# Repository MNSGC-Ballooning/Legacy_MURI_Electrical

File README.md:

# LEGACY_MURI_Electrical
Legacy repository containing EAGLE schematics and PCB files for MURI related payloads. For the newest designs, see MURI_Electric.

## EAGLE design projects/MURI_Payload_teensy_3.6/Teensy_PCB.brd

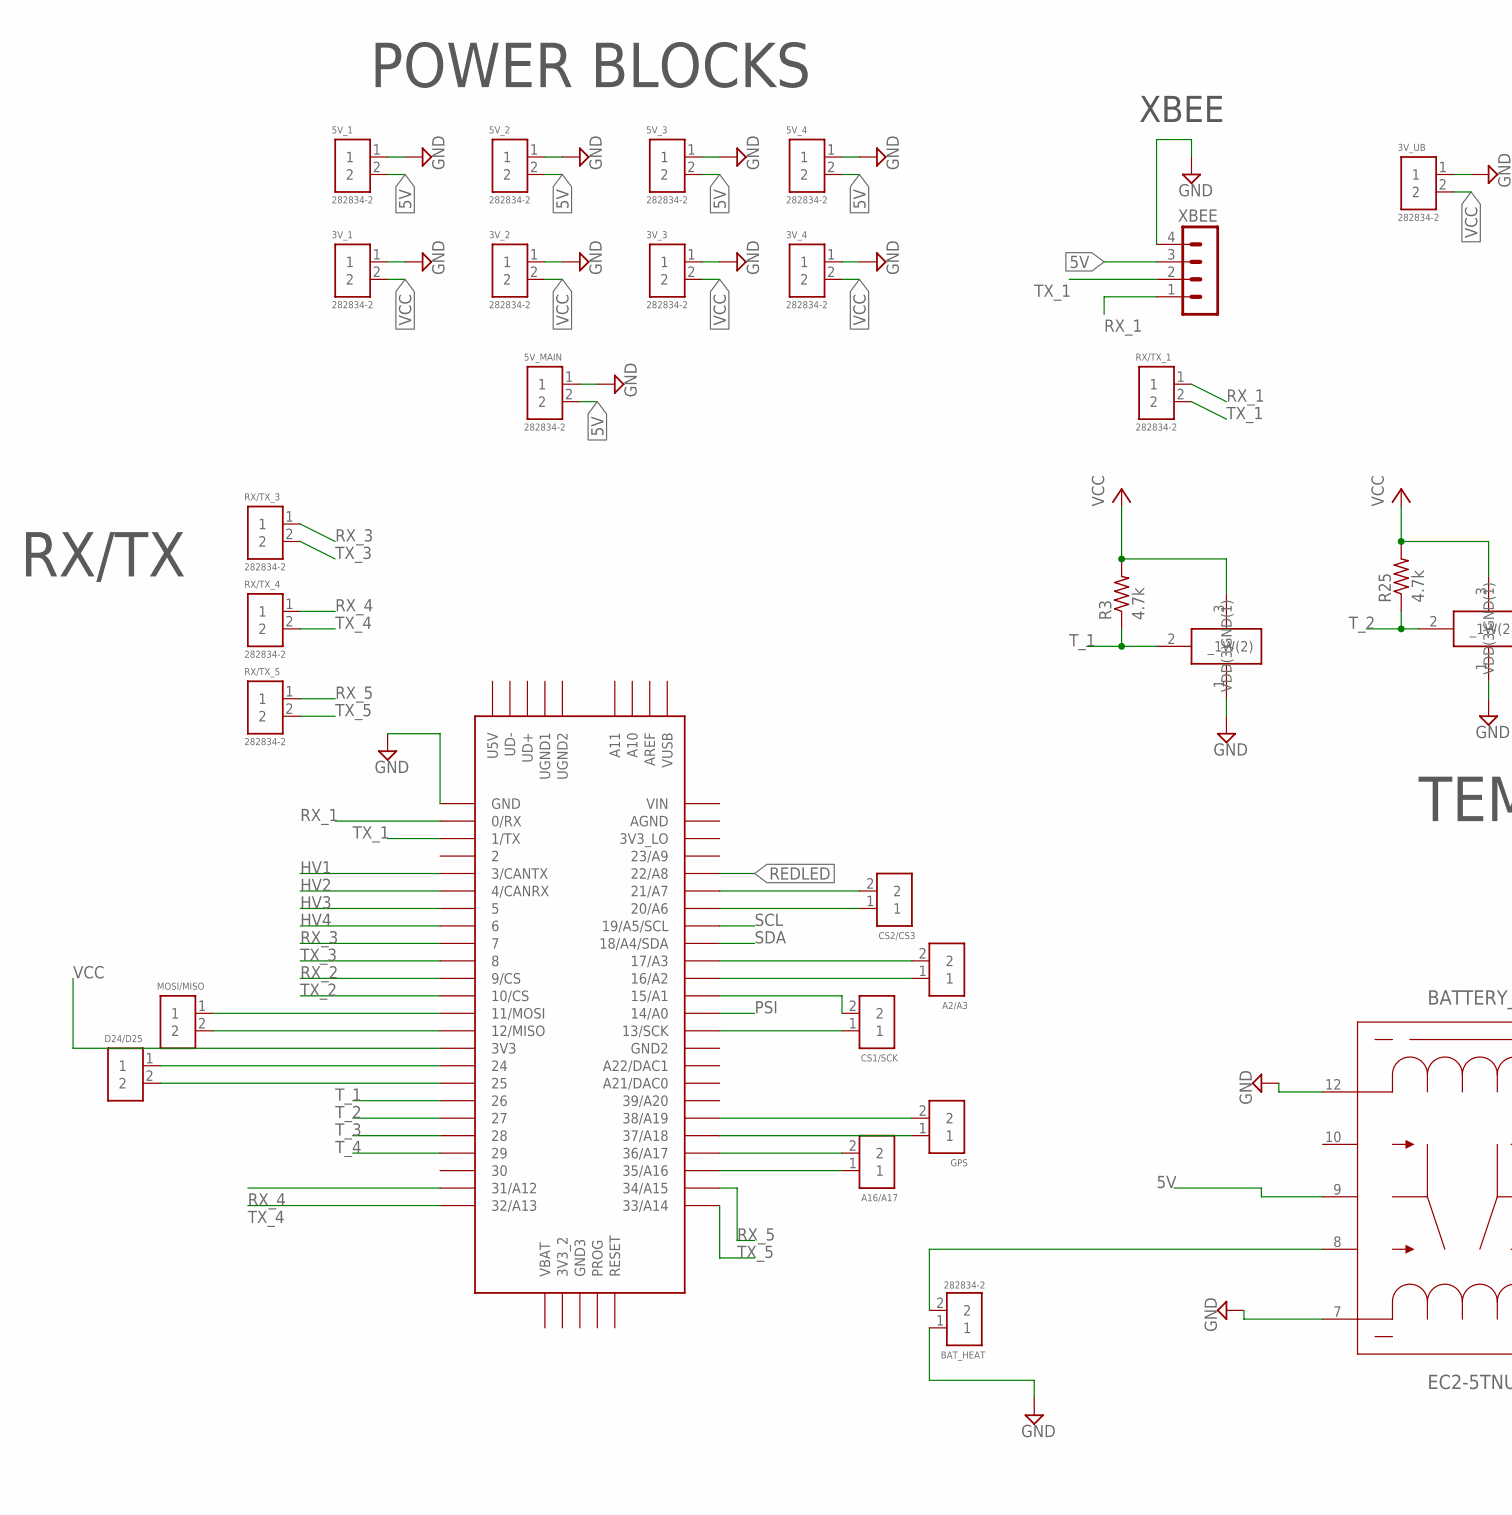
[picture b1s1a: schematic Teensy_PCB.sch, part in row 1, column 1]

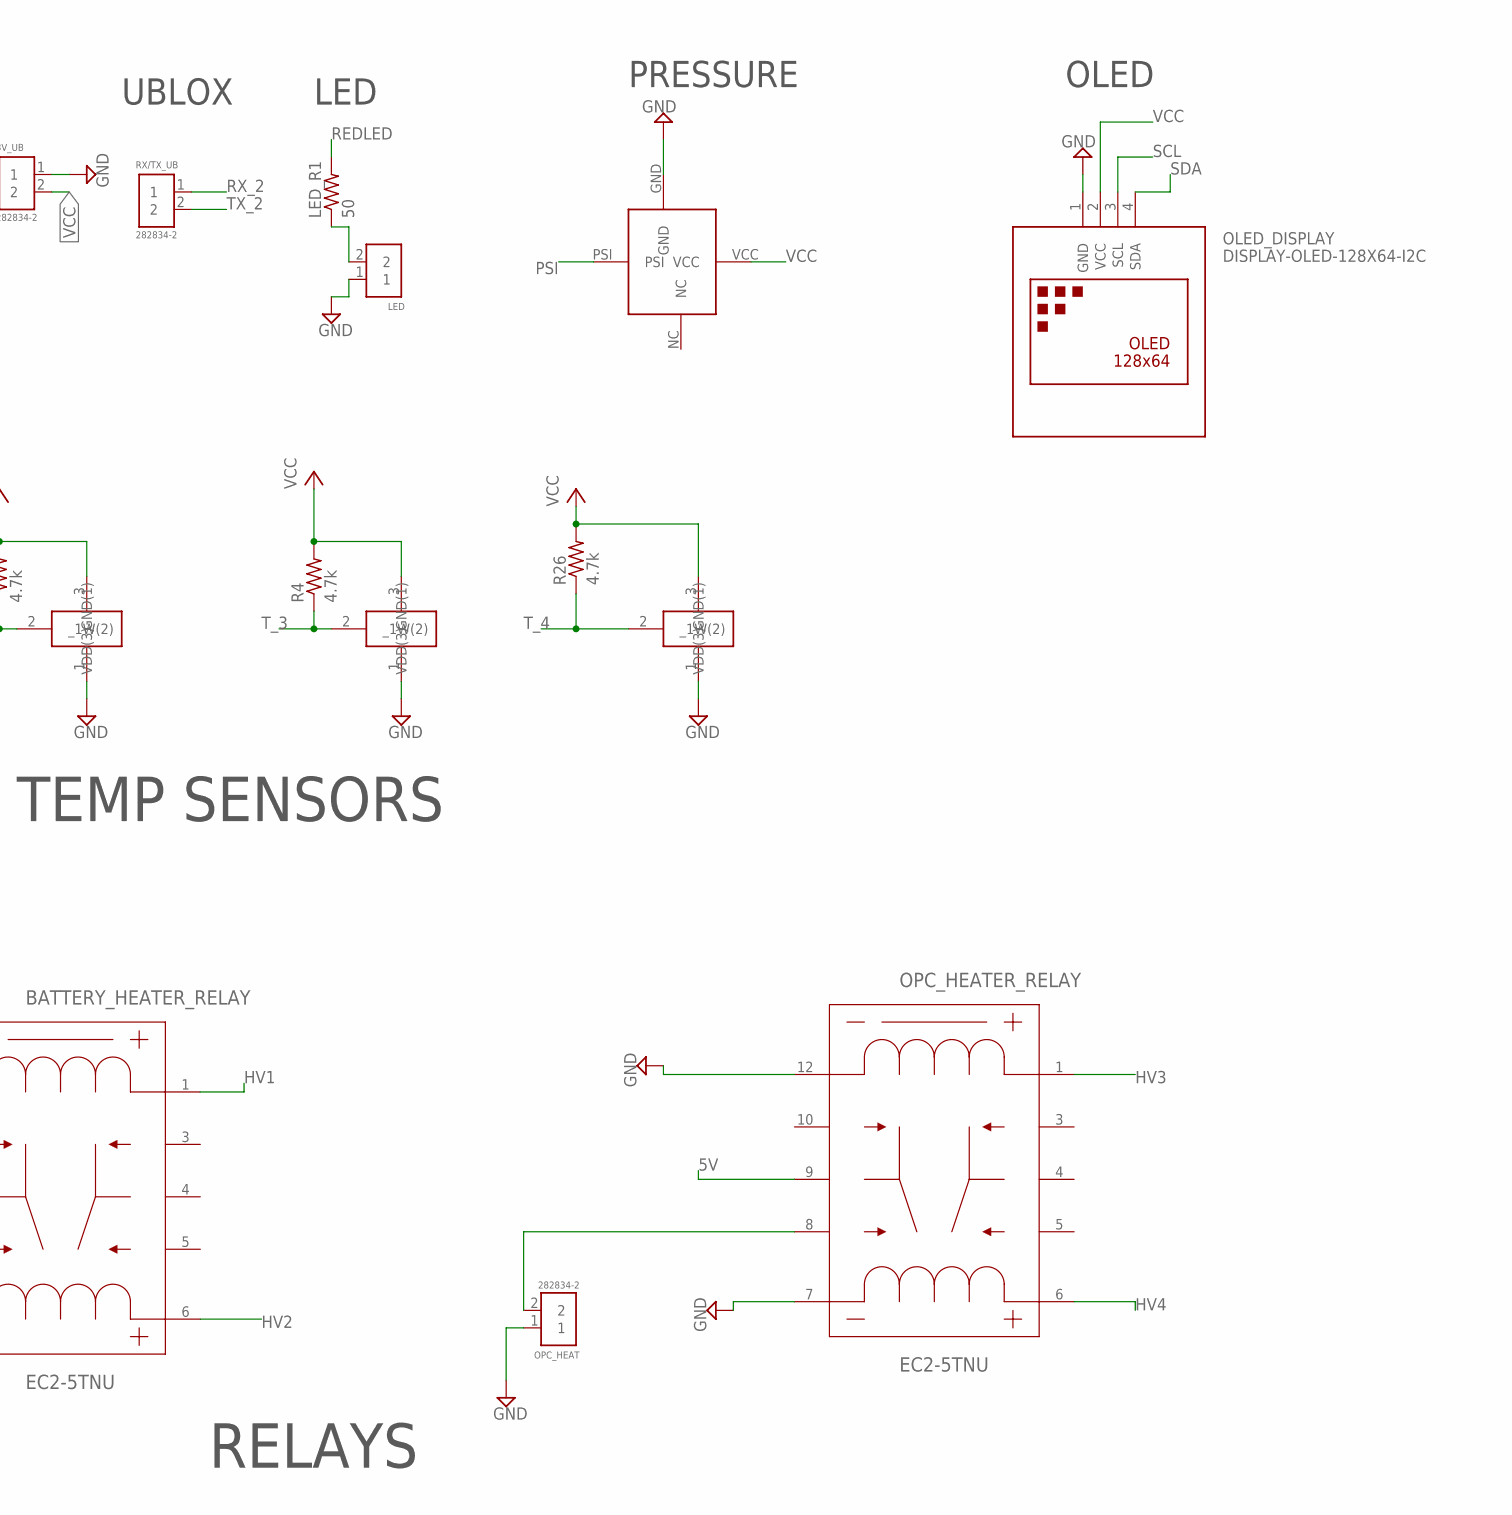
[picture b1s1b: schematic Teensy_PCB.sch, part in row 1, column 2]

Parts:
3V_1, 3V_2, 3V_3, 3V_4, 3V_UB, 5V_1, 5V_2, 5V_3, 5V_4, 5V_MAIN: 282834-2; CONN_282834-2
A2/A3, A16/A17: 282834-2; CONN_282834-2
BATTERY_HEATER_RELAY: EC2-5TNU; EC2TNU
BAT_HEAT: 282834-2; CONN_282834-2
CS1/SCK, CS2/CS3: 282834-2; CONN_282834-2
D24/D25: 282834-2; CONN_282834-2
GPS: 282834-2; CONN_282834-2
LED: 282834-2; CONN_282834-2
LED_R1: 50; 0204/7
MOSI/MISO: 282834-2; CONN_282834-2
OLED_DISPLAY: DISPLAY-OLED-128X64-I2C
OPC_HEAT: 282834-2; CONN_282834-2
OPC_HEATER_RELAY: EC2-5TNU; EC2TNU
PRESSURE_SENSOR: SSCSANN015PAAA5
R3, R4, R25, R26: 4.7k; 0204/7
RX/TX_1, RX/TX_3, RX/TX_4, RX/TX_5: 282834-2; CONN_282834-2
RX/TX_UB: 282834-2; CONN_282834-2
TEMP_1, TEMP_2, TEMP_3, TEMP_4: DS18B20.2; TO92-
U$1: TEENSY_3.5/3.6
XBEE: MA04-1

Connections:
5V: 5V_1.2, 5V_2.2, 5V_3.2, 5V_4.2, 5V_MAIN.2, BATTERY_HEATER_RELAY.9 (8), OPC_HEATER_RELAY.9 (8), XBEE.3
GND: 3V_1.1, 3V_2.1, 3V_3.1, 3V_4.1, 3V_UB.1, 5V_1.1, 5V_2.1, 5V_3.1, 5V_4.1, 5V_MAIN.1, BATTERY_HEATER_RELAY.7 (6), BATTERY_HEATER_RELAY.12 (10), BAT_HEAT.1, LED.1, OLED_DISPLAY.1 (GND), OPC_HEAT.1, OPC_HEATER_RELAY.7 (6), OPC_HEATER_RELAY.12 (10), PRESSURE_SENSOR.GND, TEMP_1.1 (GND(1)), TEMP_2.1 (GND(1)), TEMP_3.1 (GND(1)), TEMP_4.1 (GND(1)), U$1.GND, XBEE.4
HV1: BATTERY_HEATER_RELAY.1, U$1.3/CANTX
HV2: BATTERY_HEATER_RELAY.6 (5), U$1.4/CANRX
HV3: OPC_HEATER_RELAY.1, U$1.5
HV4: OPC_HEATER_RELAY.6 (5), U$1.6
unnamed: OPC_HEAT.2, OPC_HEATER_RELAY.8 (7)
unnamed: BATTERY_HEATER_RELAY.8 (7), BAT_HEAT.2
unnamed: MOSI/MISO.1, U$1.11/MOSI
unnamed: LED.2, LED_R1.1
unnamed: MOSI/MISO.2, U$1.12/MISO
unnamed: CS1/SCK.2, U$1.15/A1
unnamed: A2/A3.2, U$1.17/A3
unnamed: CS1/SCK.1, U$1.13/SCK
unnamed: A2/A3.1, U$1.16/A2
unnamed: CS2/CS3.2, U$1.21/A7
unnamed: CS2/CS3.1, U$1.20/A6
unnamed: D24/D25.1, U$1.24
unnamed: D24/D25.2, U$1.25
unnamed: A16/A17.1, U$1.35/A16
unnamed: A16/A17.2, U$1.36/A17
unnamed: GPS.1, U$1.37/A18
unnamed: GPS.2, U$1.38/A19
PSI: PRESSURE_SENSOR.PSI, U$1.14/A0
REDLED: LED_R1.2, U$1.22/A8
RX_1: RX/TX_1.1, U$1.0/RX, XBEE.1
RX_2: RX/TX_UB.1, U$1.9/CS
RX_3: RX/TX_3.1, U$1.7
RX_4: RX/TX_4.1, U$1.31/A12
RX_5: RX/TX_5.1, U$1.34/A15
SCL: OLED_DISPLAY.3 (SCL), U$1.19/A5/SCL
SDA: OLED_DISPLAY.4 (SDA), U$1.18/A4/SDA
TX_1: RX/TX_1.2, U$1.1/TX, XBEE.2
TX_2: RX/TX_UB.2, U$1.10/CS
TX_3: RX/TX_3.2, U$1.8
TX_4: RX/TX_4.2, U$1.32/A13
TX_5: RX/TX_5.2, U$1.33/A14
T_1: R3.1, TEMP_1.2 (_1W(2)), U$1.26
T_2: R25.1, TEMP_2.2 (_1W(2)), U$1.27
T_3: R4.1, TEMP_3.2 (_1W(2)), U$1.28
T_4: R26.1, TEMP_4.2 (_1W(2)), U$1.29
VCC: 3V_1.2, 3V_2.2, 3V_3.2, 3V_4.2, 3V_UB.2, OLED_DISPLAY.2 (VCC), PRESSURE_SENSOR.VCC, R3.2, R4.2, R25.2, R26.2, TEMP_1.3 (VDD(3)), TEMP_2.3 (VDD(3)), TEMP_3.3 (VDD(3)), TEMP_4.3 (VDD(3)), U$1.3V3

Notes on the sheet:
RX/TX
TEMP SENSORS
RELAYS
POWER BLOCKS
XBEE
UBLOX
LED
PRESSURE
OLED

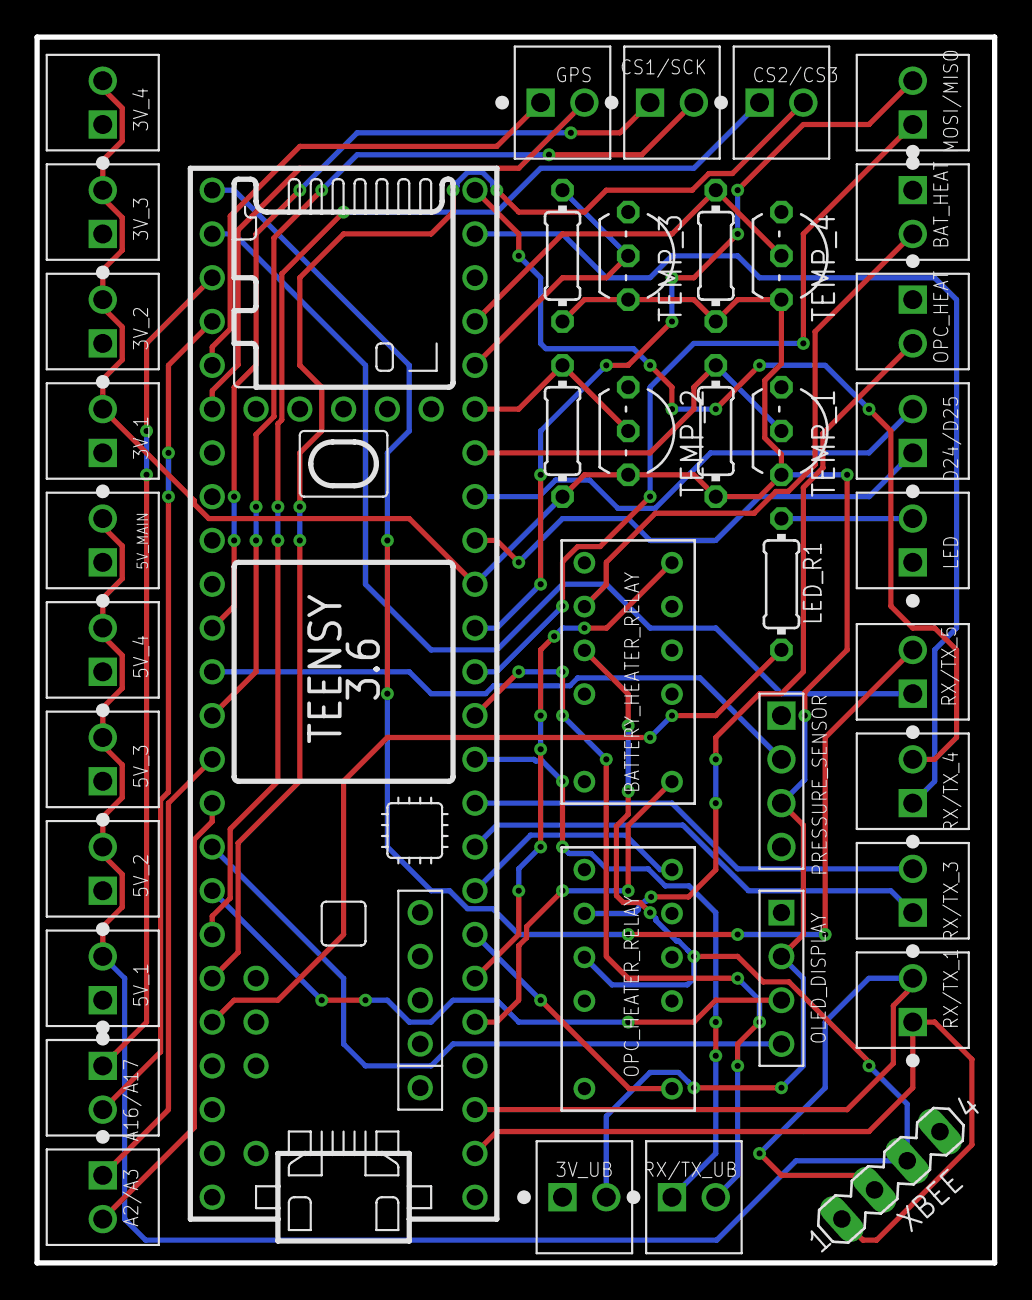
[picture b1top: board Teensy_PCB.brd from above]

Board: 2 copper layers, 55.5 x 71.1 mm, 40 parts (0 on the bottom side), 42 nets.

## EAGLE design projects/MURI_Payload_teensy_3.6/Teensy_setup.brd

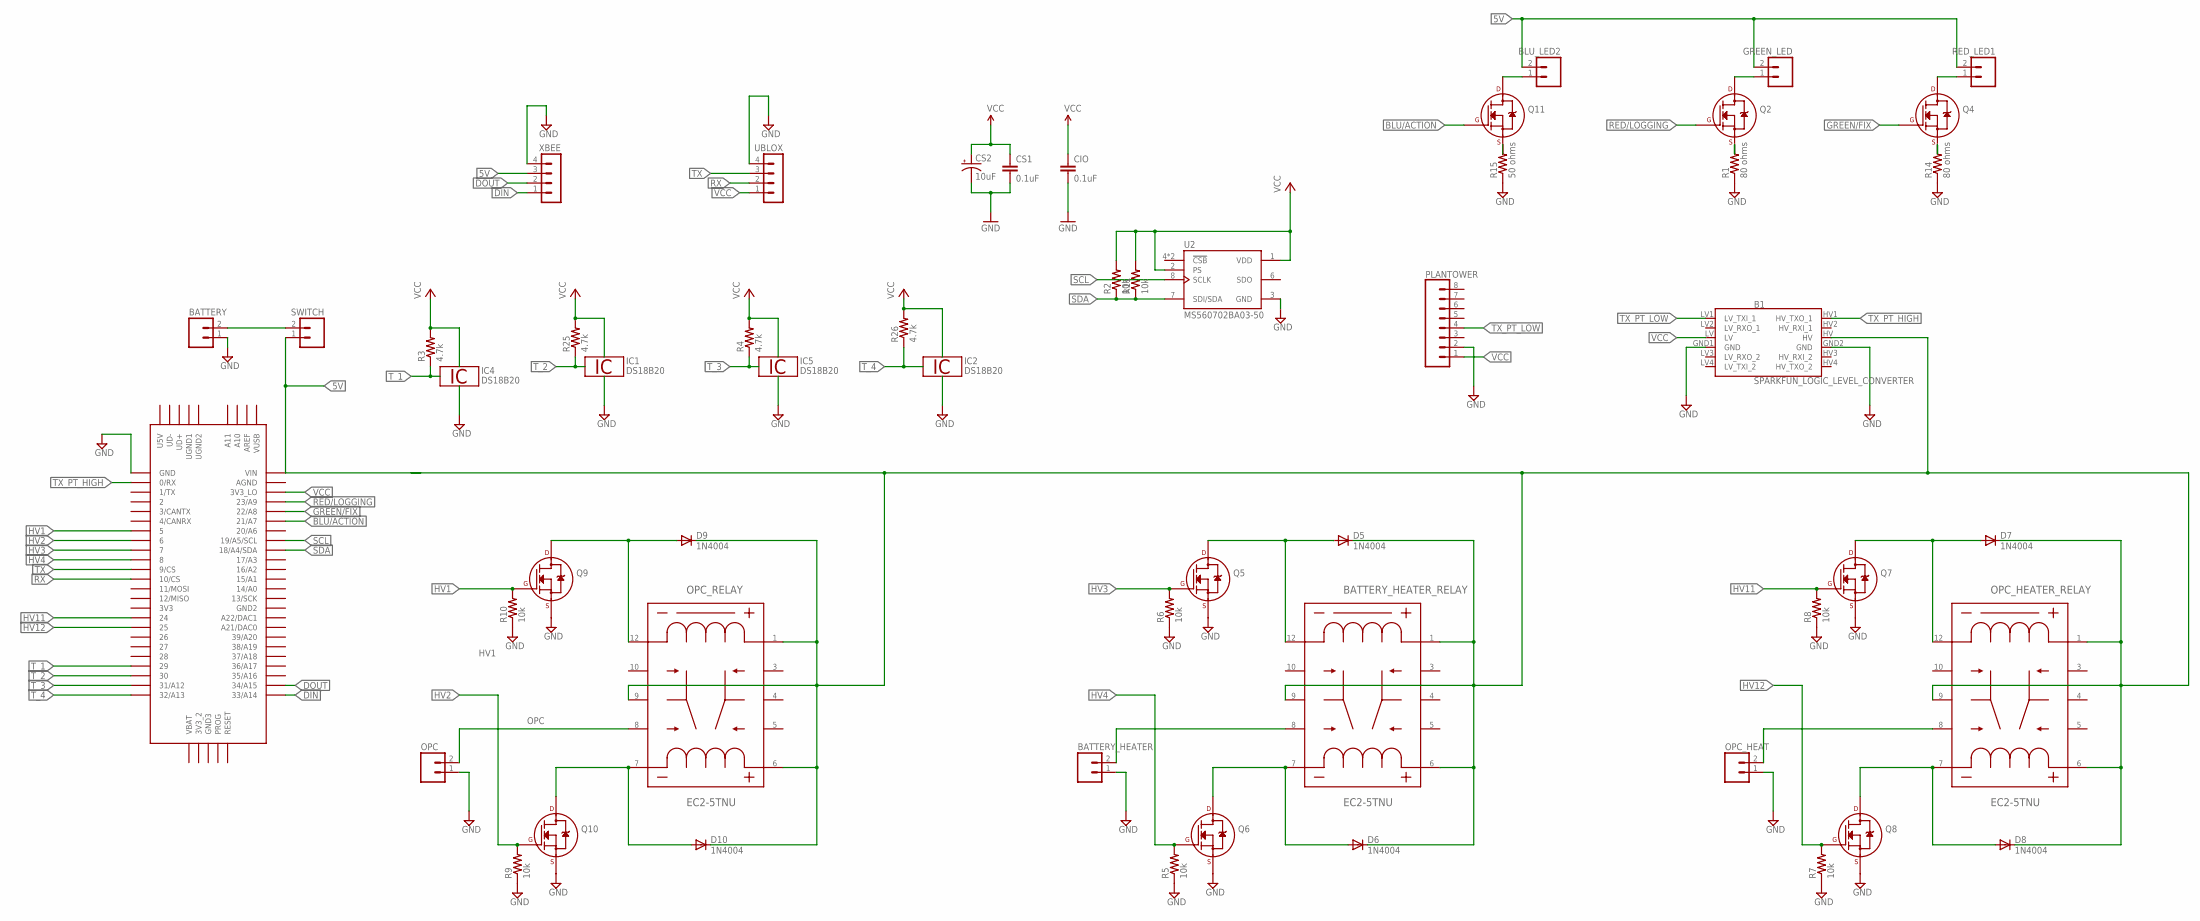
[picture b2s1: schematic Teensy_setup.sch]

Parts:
B1: SPARKFUN_LOGIC_LEVEL_CONVERTER
BATTERY: M02; 02P
BATTERY_HEATER: M02; 02P
BATTERY_HEATER_RELAY: EC2-5TNU; EC2TNU
BLU_LED2: M02; 02P
CIO: 0.1uF; 0402-CAP
CS1: 0.1uF; 0402-CAP
CS2: 10uF; EIA3216
D5, D6, D7, D8, D9, D10: 1N4004; DO41-10
GREEN_LED: M02; 02P
IC1, IC2, IC4, IC5: DS18B20; TO92-
OPC: M02; 02P
OPC_HEAT: M02; 02P
OPC_HEATER_RELAY: EC2-5TNU; EC2TNU
OPC_RELAY: EC2-5TNU; EC2TNU
PLANTOWER: CONN_08"; 1X08
Q2, Q4, Q5, Q6, Q7, Q8, Q9, Q10, Q11: 2N7000_TO92; TO-92
R1, R14: 80 ohms; 0207/7
R2, R11: 10k; 0204/7
R3, R4, R25, R26: 4.7k; 0204/7
R5, R6, R7, R8, R9, R10: 10k; 0207/7
R15: 50 ohms; 0207/7
RED_LED1: M02; 02P
SWITCH: M02; 02P
U2: MS560702BA03-50; SON125P300X500X100-8N
U$1: TEENSY_3.5/3.6
UBLOX: MA04-1
XBEE: MA04-1

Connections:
1W: IC1.2 (1W), IC2.2 (1W), IC4.2 (1W), IC5.2 (1W)
5V: BLU_LED2.2, GREEN_LED.2, RED_LED1.2, SWITCH.1, U$1.VIN, XBEE.3
5V2: B1.HV, BATTERY_HEATER_RELAY.1, BATTERY_HEATER_RELAY.6 (5), BATTERY_HEATER_RELAY.9 (8), D5.C, D6.C, D7.C, D8.C, D9.C, D10.C, OPC_HEATER_RELAY.1, OPC_HEATER_RELAY.6 (5), OPC_HEATER_RELAY.9 (8), OPC_RELAY.1, OPC_RELAY.6 (5), OPC_RELAY.9 (8)
BATTERY_HEATER: OPC_HEAT.2, OPC_HEATER_RELAY.8 (7)
BLU/ACTION: Q11.2 (G), U$1.21/A7
DIN: U$1.33/A14, XBEE.1
DOUT: U$1.34/A15, XBEE.2
GND: B1.GND1 (GND), B1.GND2 (GND), BATTERY.1, BATTERY_HEATER.1, CIO.2, CS1.2, CS2.C (-), IC1.1 (GND), IC2.1 (GND), IC4.1 (GND), IC5.1 (GND), OPC.1, OPC_HEAT.1, PLANTOWER.2, Q5.1 (S), Q6.1 (S), Q7.1 (S), Q8.1 (S), Q9.1 (S), Q10.1 (S), R1.1, R5.1, R6.1, R7.1, R8.1, R9.1, R10.1, R14.1, R15.1, U2.3 (GND), U$1.GND, UBLOX.4, XBEE.4
GREEN/FIX: Q4.2 (G), U$1.22/A8
HV1: Q9.2 (G), R10.2, U$1.5
HV2: Q10.2 (G), R9.2, U$1.6
HV3: Q5.2 (G), R6.2, U$1.7
HV4: Q6.2 (G), R5.2, U$1.8
HV11: Q7.2 (G), R8.2, U$1.24
HV12: Q8.2 (G), R7.2, U$1.25
unnamed: BATTERY.2, SWITCH.2
unnamed: Q2.1 (S), R1.2
unnamed: GREEN_LED.1, Q2.3 (D)
unnamed: Q4.1 (S), R14.2
unnamed: BATTERY_HEATER_RELAY.12 (10), D5.A, Q5.3 (D)
unnamed: BATTERY_HEATER_RELAY.7 (6), D6.A, Q6.3 (D)
unnamed: D7.A, OPC_HEATER_RELAY.12 (10), Q7.3 (D)
unnamed: D8.A, OPC_HEATER_RELAY.7 (6), Q8.3 (D)
unnamed: D9.A, OPC_RELAY.12 (10), Q9.3 (D)
unnamed: D10.A, OPC_RELAY.7 (6), Q10.3 (D)
unnamed: Q4.3 (D), RED_LED1.1
unnamed: Q11.1 (S), R15.2
unnamed: BLU_LED2.1, Q11.3 (D)
OPC: BATTERY_HEATER.2, BATTERY_HEATER_RELAY.8 (7), OPC.2, OPC_RELAY.8 (7)
RED/LOGGING: Q2.2 (G), U$1.23/A9
RX: U$1.10/CS, UBLOX.2
SCL: U2.8 (SCLK), U$1.19/A5/SCL
SDA: R2.1, R11.1, U2.7 (SDI/SDA), U$1.18/A4/SDA
TX: U$1.9/CS, UBLOX.3
TX_PT_HIGH: B1.HV1 (HV_TXO_1), U$1.0/RX
TX_PT_LOW: B1.LV1 (LV_TXI_1), PLANTOWER.4
T_1: R3.1, U$1.29
T_2: R25.1, U$1.30
T_3: R4.1, U$1.31/A12
T_4: R26.1, U$1.32/A13
VCC: B1.LV, CIO.1, CS1.1, CS2.A (+), PLANTOWER.1, R2.2, R3.2, R4.2, R11.2, R25.2, R26.2, U2.1 (VDD), U2.2 (PS), U$1.3V3_LO, UBLOX.1
VDD: IC1.3 (VDD), IC2.3 (VDD), IC4.3 (VDD), IC5.3 (VDD)

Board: 2 copper layers, 54 parts (0 on the bottom side), 42 nets, no tracks yet.

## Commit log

2019-03-07 Added all MURI electrical schematics to new repo
2019-04-09 Finished external SMART schematic rev1.
2019-04-19 Fixed my stupid shit.
2019-04-19 Added Xbee and UBlox.
2019-04-23 Added pin connections for XBee.
2019-04-29 I'm an idiot.
2019-05-28 Got rid of an assigned pin from a depricated sensor.
2019-06-04 Fixed wiring of MS5607 and updated external SMART schematic.
2019-06-17 Added edits to teensy 3.6 schematic for the plantower. Added stuff from EAGLE intro presentation.
2019-06-20 I wired up the first iteration of the PCB and added terminal blocks to the schematic
2019-09-28 Version 1 of board, no routing done, incomplete
2020-01-10 Second iteration of printed board with CAMOutputs
2020-01-14 Second finalized iteration of PCB
2020-01-14 New libraries for second iteration
2020-05-22 General Ballooning PCB libraries added

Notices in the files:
parts and their libraries:
diy-modules: Released under the Creative Commons Attribution 4.0 International License: http://creativecommons.org/licenses/by/4.0
SparkFun-Boards: Licensing: Creative Commons ShareAlike 4.0 International - https://creativecommons.org/licenses/by-sa/4.0
